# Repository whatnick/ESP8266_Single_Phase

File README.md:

This project contains parts from:

# Whatnick-ATM90E26 Breakout
PCB files for the Whatnick ATM90E26 Breakout

For more details, check out the product page at

  * https://www.tindie.com/products/whatnick/atm90e26-breakout/
  
Whatnick invests time and resources providing this open source design, please support Whatnick and open-source hardware by purchasing products from the Tindie Store!

Designed by Tisham Dhar/whatnick for Whatnick INC.
Creative Commons Attribution/Share-Alike, all text above must be included in any redistribution

# Adafruit-Feather-ESP8266-HUZZAH-PCB
PCB files for the Adafruit Feather ESP8266 HUZZAH

For more details, check out the product page at

  * https://www.adafruit.com/product/2821

# Adafruit-Adalogger-FeatherWing-PCB
PCB files for the Adalogger FeatherWing

For more details, check out the product page at

* https://www.adafruit.com/product/2922

Format is EagleCAD schematic and board layout

Adafruit invests time and resources providing this open source design, please support Adafruit and open-source hardware by purchasing products from Adafruit!

Designed by Limor Fried/Ladyada for Adafruit Industries.
Creative Commons Attribution/Share-Alike, all text above must be included in any redistribution

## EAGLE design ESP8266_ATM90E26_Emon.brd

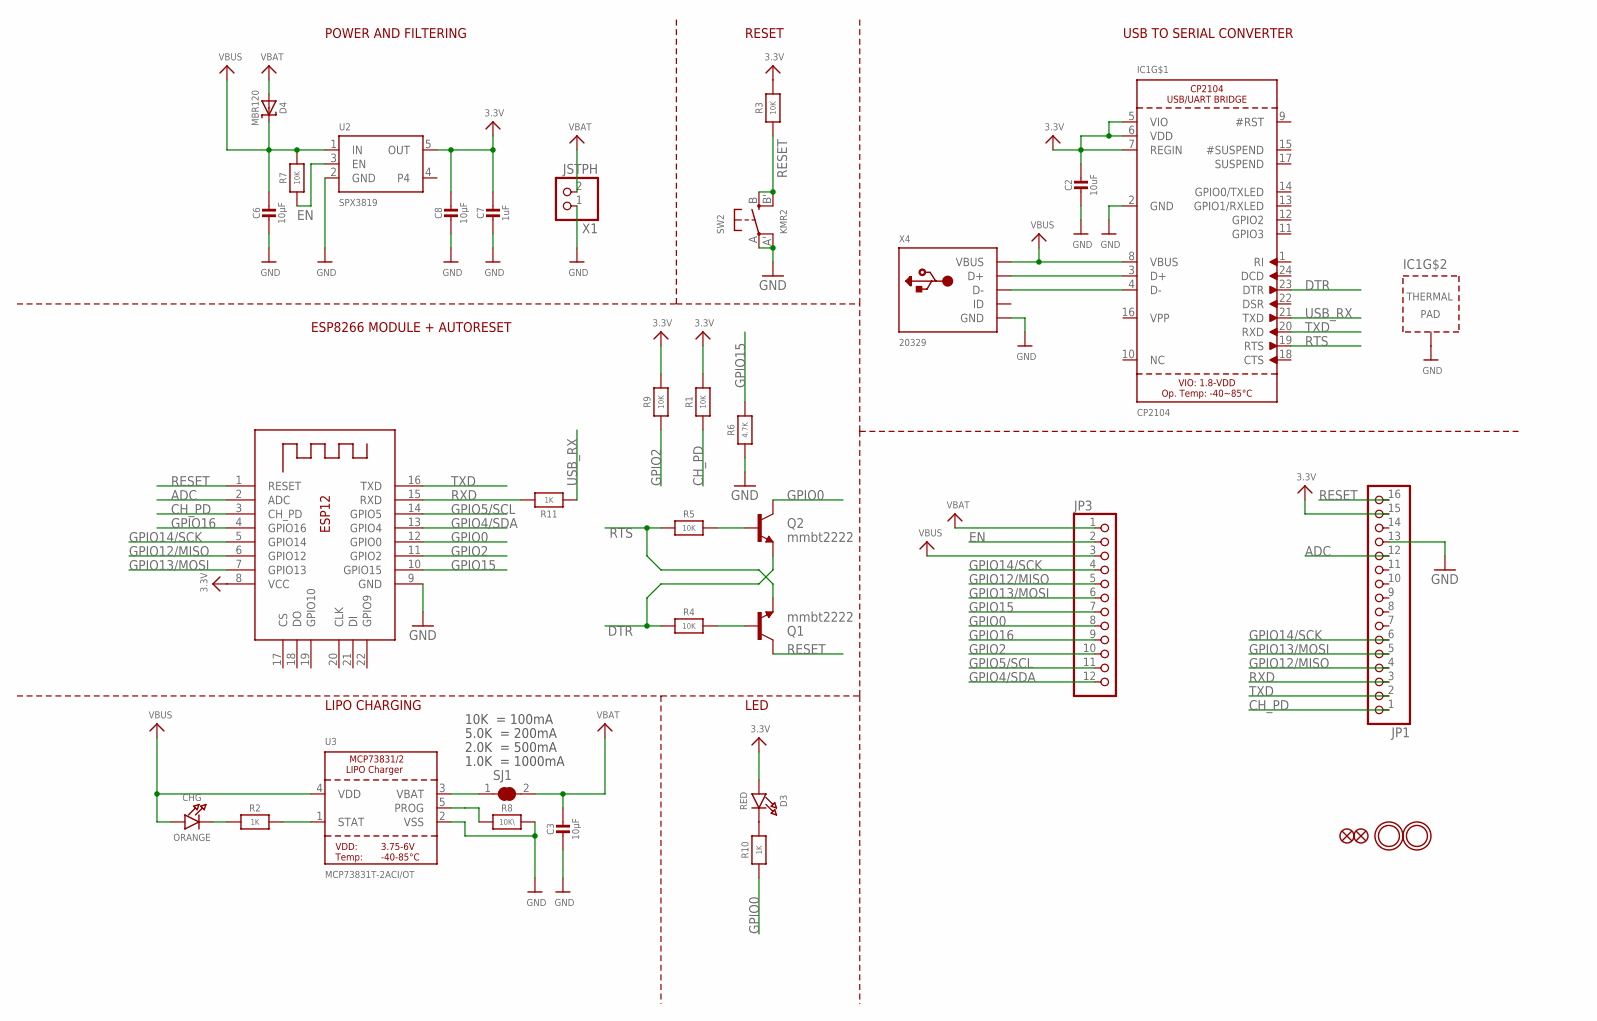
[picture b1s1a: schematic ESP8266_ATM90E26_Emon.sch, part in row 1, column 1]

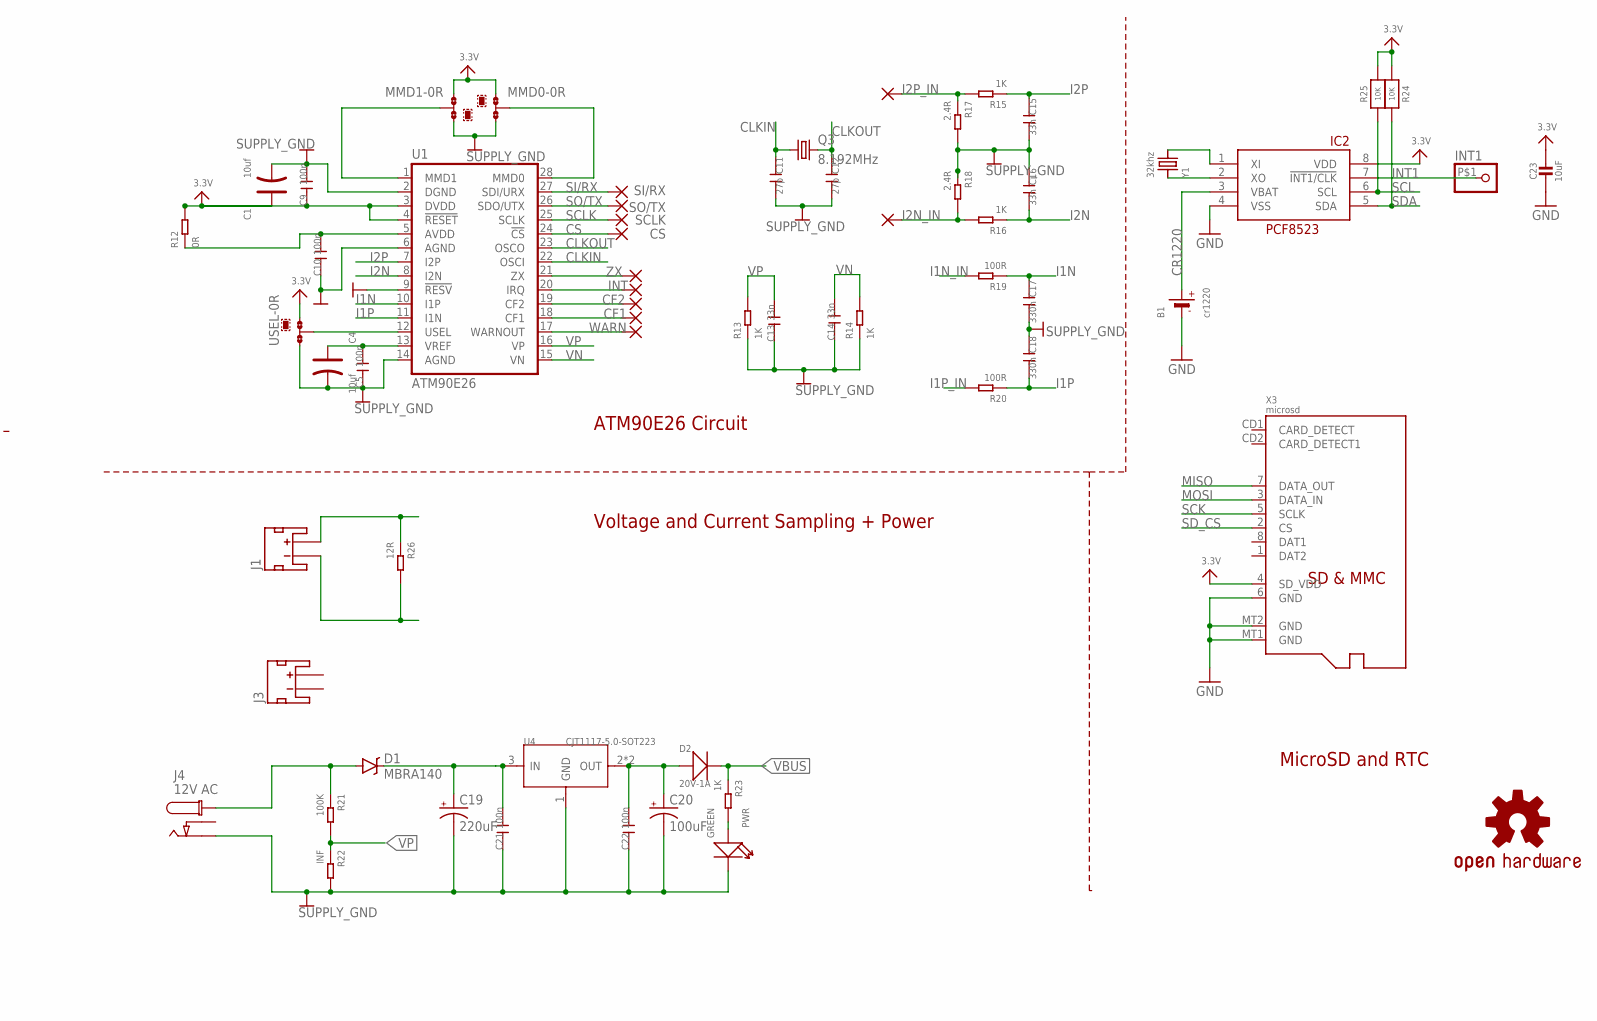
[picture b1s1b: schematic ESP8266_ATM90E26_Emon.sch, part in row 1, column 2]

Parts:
B1: cr1220; CR1220
C1, C4: 10uf; AVX-A
C2, C23: 10uF; 0603-NO
C3, C6, C8: 10µF; 0603-NO
C5, C9, C10, C21, C22: 100n; C0603
C7: 1uF; 0603-NO
C11, C12: 27p; C0603
C13, C14, C15, C16: 33n; C0603
C17, C18: 330n; C0603
C19: 220uF; 140CLH-1010
C20: 100uF; 153CLV-0605
CF1, CF2: WIREPADSMD1,27-254; SMD1,27-2,54
CHG: ORANGE; CHIPLED_0603_NOOUTLINE
CS: WIREPADSMD1,27-254; SMD1,27-2,54
D1: MBRA140; SMA-DIODE
D2: 20V-1A; SOD-123
D3: RED; CHIPLED_0805_NOOUTLINE
D4: MBR120; SOD-123
I2N_IN, I2P_IN: WIREPADSMD1,27-254; SMD1,27-2,54
IC1: CP2104; QFN24_4MM_SMSC
IC2: RTC_PCF8523T; SOIC8_150MIL
INT: WIREPADSMD1,27-254; SMD1,27-2,54
INT1: HEADER-1X1-SMD-MASKHELD_1X2MM; 1X01_SMD_MASKHELD_1X2MM
J1, J3: JST_2MM_MALE; JST-2-SMD
J4: 12V AC; DC_BARREL_JACK_SMD_2MM
JP1: HEADER-1X16ROUND; 1X16_ROUND
JP3: HEADER-1X12; 1X12_ROUND
LOGO1: OSHW-LOGOS; OSHW-LOGO-S
MMD0, MMD1: 0R-JUMPA; A0R-JMP
PWR: GREEN; LED-0603
Q1, Q2: mmbt2222; SOT23-3
Q3: 8.192MHz; HC49UP
R1, R3, R4, R7, R9, R24, R25: 10K; 0603-NO
R2, R10: 1K; 0603-NO
R5: 10K; _0603MP
R6: 4.7K; 0603-NO
R8: 10K\; 0603-NO
R11: 1K; _0603MP
R12: 0R; R0603
R13, R14, R15, R16, R23: 1K; R0603
R17, R18: 2.4R; R0603
R19, R20: 100R; R0603
R21: 100K; R0603
R22: INF; R0603
R26: 12R; R0603
SCLK: WIREPADSMD1,27-254; SMD1,27-2,54
SI/RX: WIREPADSMD1,27-254; SMD1,27-2,54
SJ1: SOLDERJUMPER_CLOSED; SOLDERJUMPER_CLOSEDWIRE
SO/TX: WIREPADSMD1,27-254; SMD1,27-2,54
SW2: KMR2; BTN_KMR2_4.6X2.8
U1: ATM90E26; SSOP-28
U2: SPX3819; SOT23-5
U3: MCP73831T-2ACI/OT; SOT23-5
U4: CJT1117-5.0-SOT223; SOT-223
U$31, U$32: MOUNTINGHOLE2.5; MOUNTINGHOLE_2.5_PLATED
U$34, U$35: FIDUCIAL""; FIDUCIAL_1MM
USEL: 0R-JUMPA; A0R-JMP
WARN: WIREPADSMD1,27-254; SMD1,27-2,54
X1: JSTPH; JSTPH2
X2: ESP-12; ESP-12E
X3: microsd; MICROSD
X4: 20329; 4UCONN_20329_V2
Y1: 32khz; CRYSTAL_8X3.8
ZX: WIREPADSMD1,27-254; SMD1,27-2,54

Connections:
3.3V: C1.+, C2.1, C7.1, C8.1, C9.1, C23.1, D3.A, IC1.5 (VIO), IC1.6 (VDD), IC1.7 (REGIN), IC2.8 (VDD), JP1.15, MMD0.1, MMD1.2, MMD1.3, R1.2, R3.2, R9.2, R12.2, R24.2, R25.2, U1.1 (MMD1), U1.3 (DVDD), U1.4 (!RESET), U2.5 (OUT), USEL.1, X2.8 (VCC), X3.4 (SD_VDD)
ADC: JP1.12, X2.2 (ADC)
CH_PD: JP1.1, R1.1, X2.3 (CH_PD)
CLKIN: C11.1, Q3.1, U1.22 (OSCI)
CLKOUT: C12.1, Q3.2, U1.23 (OSCO)
CR1220: B1.+$1 (+), IC2.3 (VBAT)
CS: CS.1, U1.24 (!CS)
DTR: IC1.23 (DTR), Q2.2 (E), R4.1
EN: JP3.2, R7.1, U2.3 (EN)
GND: B1.-, C1.-, C2.2, C3.2, C4.-, C5.1, C6.2, C7.2, C8.2, C9.2, C10.1, C11.2, C12.2, C13.1, C14.1, C15.2, C16.1, C17.2, C18.1, C19.-, C20.-, C21.1, C22.1, C23.2, IC1.2 (GND), IC1.THERM (TP), IC2.4 (VSS), J4.P2, JP1.13, MMD0.3, MMD1.1, PWR.-, R6.1, R8.2, R13.1, R14.1, R17.2, R18.1, R22.2, SW2.A, SW2.A' (P1), U1.2 (DGND), U1.6 (AGND), U1.9 (!RESV), U1.14 (AGND), U2.2 (GND), U3.2 (VSS), U4.1 (GND), USEL.3, X1.1, X2.9 (GND), X3.6 (GND), X3.MT1 (GND), X3.MT2 (GND), X4.BASE@1 (GND), X4.BASE@2 (GND), X4.GND, X4.SPRT@1 (GND), X4.SPRT@2 (GND), X4.SPRT@3 (GND), X4.SPRT@4 (GND)
GPIO0: JP3.8, Q2.3 (C), R10.1, X2.12 (GPIO0)
GPIO2: JP3.10, R9.1, X2.11 (GPIO2)
GPIO4/SDA: JP3.12, X2.13 (GPIO4)
GPIO5/SCL: JP3.11, X2.14 (GPIO5)
GPIO12/MISO: JP1.4, JP3.5, X2.6 (GPIO12)
GPIO13/MOSI: JP1.5, JP3.6, X2.7 (GPIO13)
GPIO14/SCK: JP1.6, JP3.4, X2.5 (GPIO14)
GPIO15: JP3.7, R6.2, X2.10 (GPIO15)
GPIO16: JP3.9, X2.4 (GPIO16)
I1N: C17.1, R19.1, U1.10 (I1P)
I1N_IN: R19.2
I1N_IN1: J1.1 (-), R26.2
I1P: C18.2, R20.1, U1.11 (I1N)
I1P_IN: R20.2
I1P_IN1: J1.2 (+), R26.1
I2N: C16.2, R16.1, U1.8 (I2N)
I2N_IN: I2N_IN.1, R16.2, R18.2
I2P: C15.1, R15.1, U1.7 (I2P)
I2P_IN: I2P_IN.1, R15.2, R17.1
INT1: IC2.7 (!INT1/CLK), INT1.P$1
MISO: X3.7 (DATA_OUT)
MOSI: X3.3 (DATA_IN)
unnamed: CHG.C, R2.1
unnamed: IC1.3 (D+), X4.D+
unnamed: R2.2, U3.1 (STAT)
unnamed: R8.1, U3.5 (PROG)
unnamed: D3.C, R10.2
unnamed: IC1.4 (D-), X4.D-
unnamed: SJ1.1, U3.3 (VBAT)
unnamed: CF2.1, U1.19 (CF2)
unnamed: MMD0.2, U1.28 (MMD0)
unnamed: CF1.1, U1.18 (CF1)
unnamed: Q1.1 (B), R4.2
unnamed: Q2.1 (B), R5.2
unnamed: C10.2, R12.1, U1.5 (AVDD)
unnamed: U1.12 (USEL), USEL.2
unnamed: D1.A, J4.P1@2 (P1), R21.1
unnamed: C19.+, C21.2, D1.C, U4.3 (IN)
unnamed: PWR.+, R23.2
unnamed: IC2.1 (XI), Y1.P$4 (2)
unnamed: U1.21 (ZX), ZX.1
unnamed: INT.1, U1.20 (IRQ)
unnamed: U1.17 (WARNOUT), WARN.1
unnamed: IC2.2 (XO), Y1.P$1 (1)
RESET: JP1.16, Q1.3 (C), R3.1, SW2.B (S), SW2.B' (S1), X2.1 (RESET)
RTS: IC1.19 (RTS), Q1.2 (E), R5.1
RXD: JP1.3, R11.2, X2.15 (RXD)
SCK: X3.5 (SCLK)
SCL: IC2.6 (SCL), R25.1
SCLK: SCLK.1, U1.25 (SCLK)
SDA: IC2.5 (SDA), R24.1
SD_CS: X3.2 (CS)
SI/RX: SI/RX.1, U1.27 (SDI/URX)
SO/TX: SO/TX.1, U1.26 (SDO/UTX)
TXD: IC1.20 (RXD), JP1.2, X2.16 (TXD)
USB_RX: IC1.21 (TXD), R11.1
VBAT: C3.1, D4.A, JP3.1, SJ1.2, X1.2
VBUS: C6.1, CHG.A, D2.-, D4.C, IC1.8 (VBUS), JP3.3, R7.2, R23.1, U2.1 (IN), U3.4 (VDD), X4.VBUS
VN: C14.2, R14.2, U1.15 (VN)
VP: C13.2, R13.2, R21.2, R22.1, U1.16 (VP)
VREF: C4.+, C5.2, U1.13 (VREF)
V_OUT: C20.+, C22.2, D2.+, U4.2 (OUT), U4.TER (OUT)

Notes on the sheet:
POWER AND FILTERING
RESET
10K = 100mA
5.0K = 200mA
2.0K = 500mA
1.0K = 1000mA
USB TO SERIAL CONVERTER
LIPO CHARGING
LED
ESP8266 MODULE + AUTORESET
ATM90E26 Circuit
Voltage and Current Sampling + Power
MicroSD and RTC

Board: 2 copper layers, 97 parts (50 on the bottom side), 66 nets, no tracks yet.

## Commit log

2016-10-26 Initial import
2016-10-26 extra line
2016-10-27 Pulled parts into 50x50mm dimension
2016-10-31 Some signal renaming
2016-12-05 Squeeze all parts into 50x50mm

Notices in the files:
parts and their libraries:
microbuilder: This work is placed in the public domain, and may be freely used for commercial and non-commercial work with the following conditions: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
SparkFun: Licensing: CC v3.0 Share-Alike You are welcome to use this library for commercial purposes.
